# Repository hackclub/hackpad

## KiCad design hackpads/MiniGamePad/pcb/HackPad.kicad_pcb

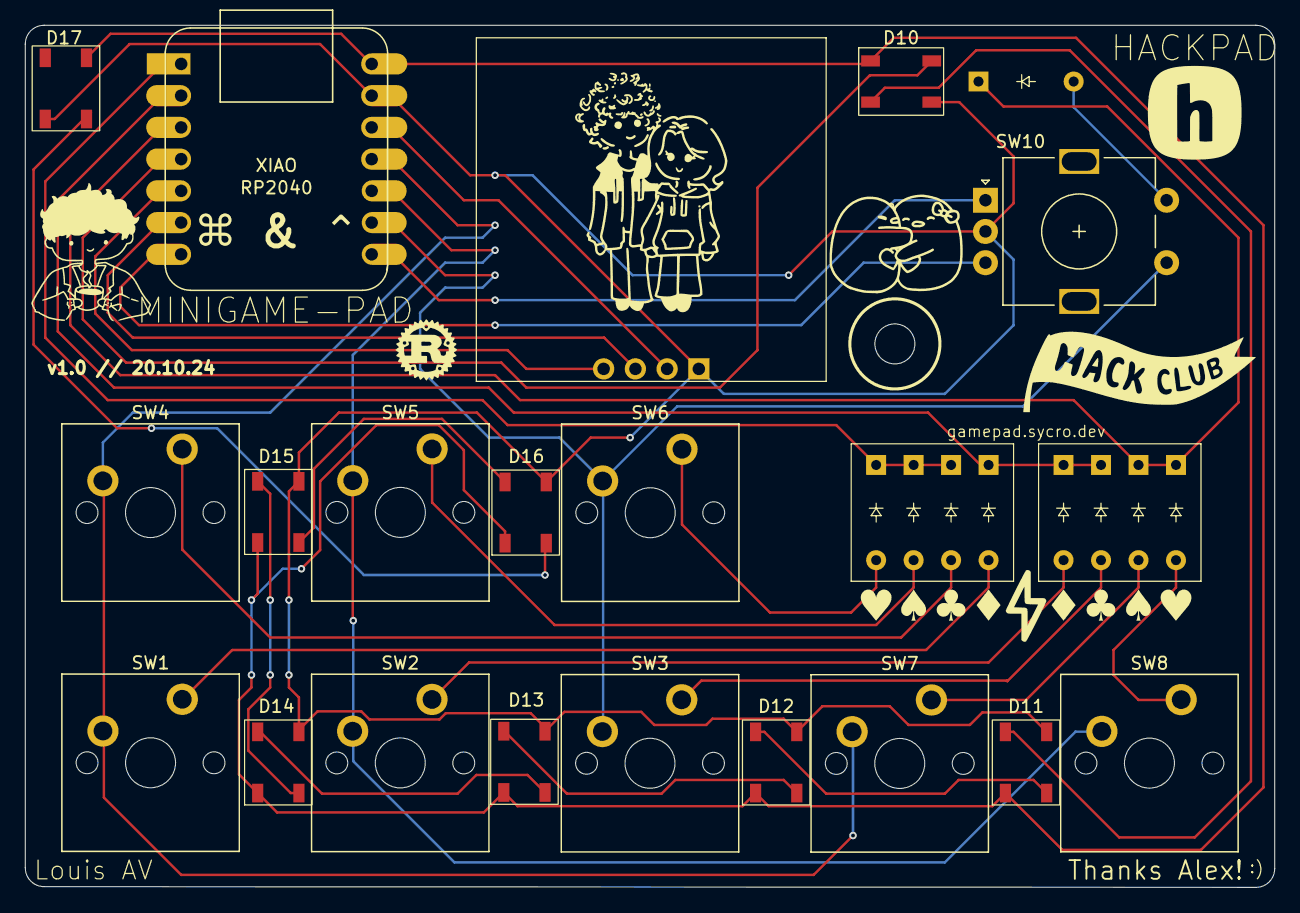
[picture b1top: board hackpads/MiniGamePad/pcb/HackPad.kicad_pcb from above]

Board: 2 copper layers, 100.0 x 69.0 mm, 28 parts (0 on the bottom side), 30 nets.

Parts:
D1, D2, D3, D4, D5, D6, D7, D8, D9: D; Diode_DO-35
D10, D11, D12, D13, D14, D15, D16, D17: WS2812B; LED_WS2812B
J1: OLED_128x64
SW1, SW2, SW3, SW4, SW5, SW6, SW7, SW8: SW_Push_45deg; MX_PCB_1.00u
SW10: RotaryEncoder_Switch; RotaryEncoder_Alps_EC11E-Switch_Vertical_H20mm
U1: MOUDLE-SEEEDUINO-XIAO; XIAO-Generic-Hybrid-14P-2.54-21X17.8MM

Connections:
+3.3V: J1.2 (VCC), U1.12 (3V3)
+5V: D10.1 (VDD), D11.1 (VDD), D12.1 (VDD), D13.1 (VDD), D14.1 (VDD), D15.1 (VDD), D16.1 (VDD), D17.1 (VDD), U1.14 (5V)
Column 1: SW1.1, SW4.1, SW7.1, U1.11 (PA6_A10_D10_MOSI)
Column 2: SW2.1, SW5.1, SW8.1, U1.10 (PA5_A9_D9_MISO)
Column 3: SW3.1, SW6.1, SW10.S1, U1.9 (PA7_A8_D8_SCK)
EC11A: SW10.A, U1.8 (PB09_A7_D7_RX)
EC11B: SW10.B, U1.7 (PB08_A6_D6_TX)
EC11SWB: D9.2 (A), SW10.S2
GND: D10.3 (VSS), D11.3 (VSS), D12.3 (VSS), D13.3 (VSS), D14.3 (VSS), D15.3 (VSS), D16.3 (VSS), D17.3 (VSS), J1.1 (GND), SW10.C, U1.13 (GND)
unnamed: D1.2 (A), SW1.2
unnamed: D2.2 (A), SW2.2
unnamed: D3.2 (A), SW3.2
unnamed: D4.2 (A), SW4.2
unnamed: D5.2 (A), SW5.2
unnamed: D6.2 (A), SW6.2
unnamed: D7.2 (A), SW7.2
unnamed: D8.2 (A), SW8.2
unnamed: D10.2 (DOUT), D11.4 (DIN)
unnamed: D11.2 (DOUT), D12.4 (DIN)
unnamed: D12.2 (DOUT), D13.4 (DIN)
unnamed: D13.2 (DOUT), D14.4 (DIN)
unnamed: D14.2 (DOUT), D15.4 (DIN)
unnamed: D15.2 (DOUT), D16.4 (DIN)
unnamed: D16.2 (DOUT), D17.4 (DIN)
RGB: D10.4 (DIN), U1.4 (PA11_A3_D3)
Row 1: D1.1 (K), D2.1 (K), D3.1 (K), U1.2 (PA4_A1_D1)
Row 2: D4.1 (K), D5.1 (K), D6.1 (K), U1.1 (PA02_A0_D0)
Row 3: D7.1 (K), D8.1 (K), D9.1 (K), U1.3 (PA10_A2_D2)
SCL: J1.3 (SCL), U1.6 (PA9_A5_D5_SCL)
SDA: J1.4 (SDA), U1.5 (PA8_A4_D4_SDA)

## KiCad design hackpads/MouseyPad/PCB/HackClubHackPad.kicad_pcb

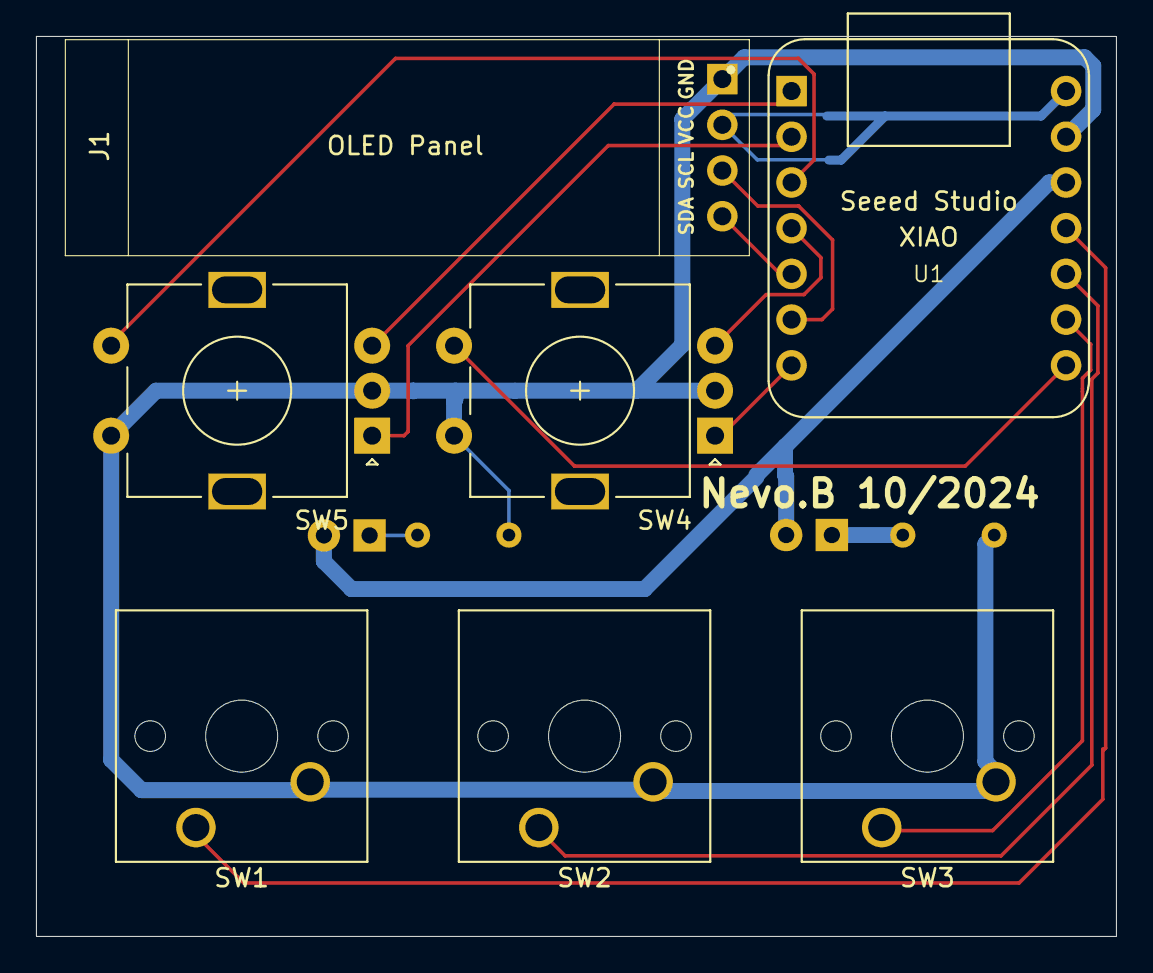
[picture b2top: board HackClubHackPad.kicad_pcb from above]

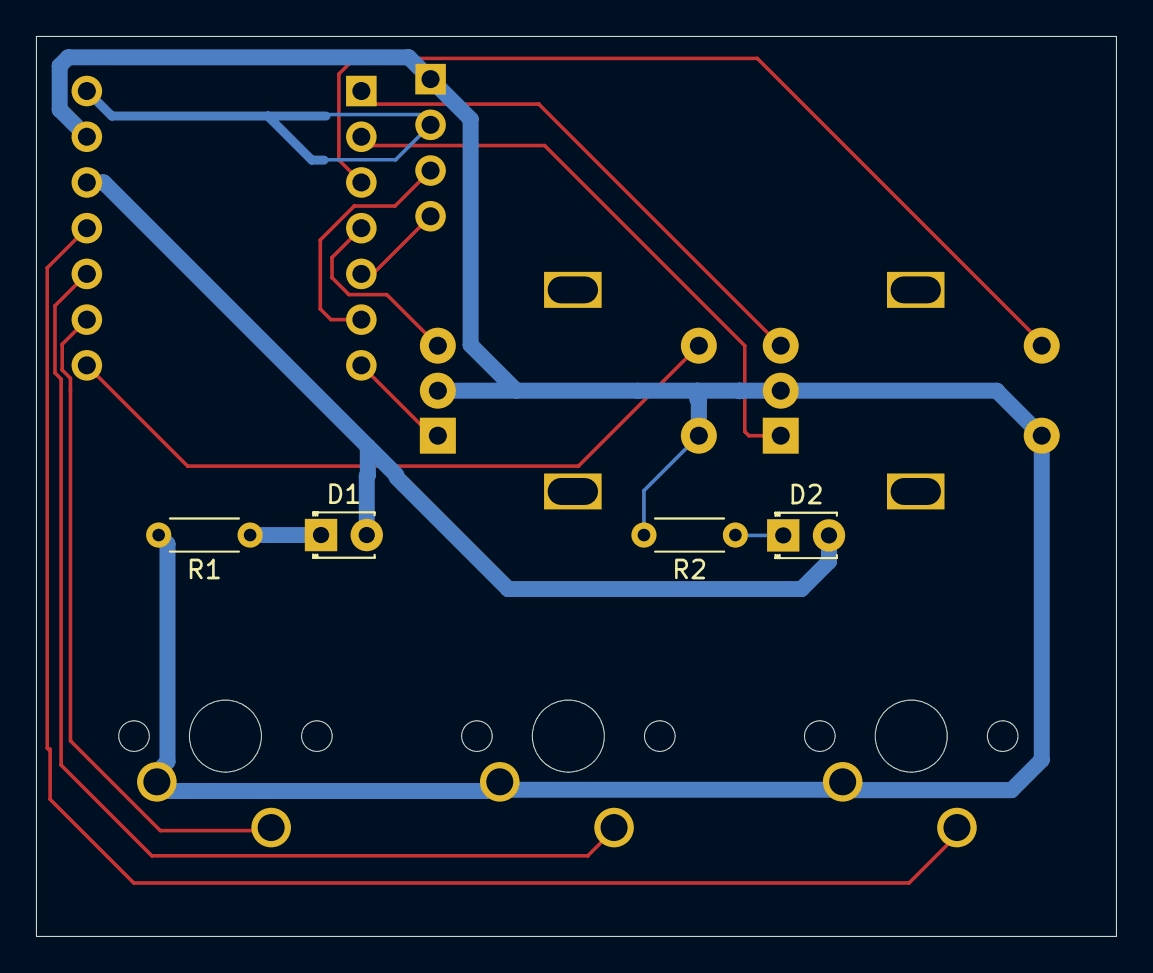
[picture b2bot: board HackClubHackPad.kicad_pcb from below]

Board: 2 copper layers, 60.0 x 50.0 mm, 11 parts (4 on the bottom side), 16 nets.

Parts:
D1, D2: LED; LED_D1.8mm_W3.3mm_H2.4mm
J1: Conn_01x04; SSD1306-0.91-OLED-4pin-128x32
R1, R2: 36; R_Axial_DIN0204_L3.6mm_D1.6mm_P5.08mm_Horizontal
SW1, SW2, SW3: SW_Push; SW_Cherry_MX_1.00u_PCB
SW4, SW5: RotaryEncoder_Switch; RotaryEncoder_Alps_EC11E-Switch_Vertical_H20mm
U1: Seeed Studio XIAO SAMD21; XIAO-Generic-Thruhole-14P-2.54-21X17.8MM

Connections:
+3.3V: D1.2 (A), D2.2 (A), U1.12 (3V3)
+5V: J1.2, U1.14 (5V)
EC11(2)A: SW4.A, U1.7 (PB08_A6_D6_TX)
EC11(2)B: SW4.B, U1.4 (PA11_A3_D3)
EC11(2)SW: SW4.S1, U1.8 (PB09_A7_D7_RX)
EC11A: SW5.A, U1.2 (PA4_A1_D1)
EC11B: SW5.B, U1.1 (PA02_A0_D0)
EC11SW: SW5.S1, U1.3 (PA10_A2_D2)
GND: J1.1, R1.2, R2.2, SW1.2, SW2.2, SW3.2, SW4.C, SW4.S2, SW5.C, SW5.S2, U1.13 (GND)
unnamed: D1.1 (K), R1.1
unnamed: D2.1 (K), R2.1
SCL: J1.3, U1.6 (PA9_A5_D5_SCL)
SDA: J1.4, U1.5 (PA8_A4_D4_SDA)
SW1: SW1.1, U1.11 (PA6_A10_D10_MOSI)
SW2: SW2.1, U1.10 (PA5_A9_D9_MISO)
SW3: SW3.1, U1.9 (PA7_A8_D8_SCK)

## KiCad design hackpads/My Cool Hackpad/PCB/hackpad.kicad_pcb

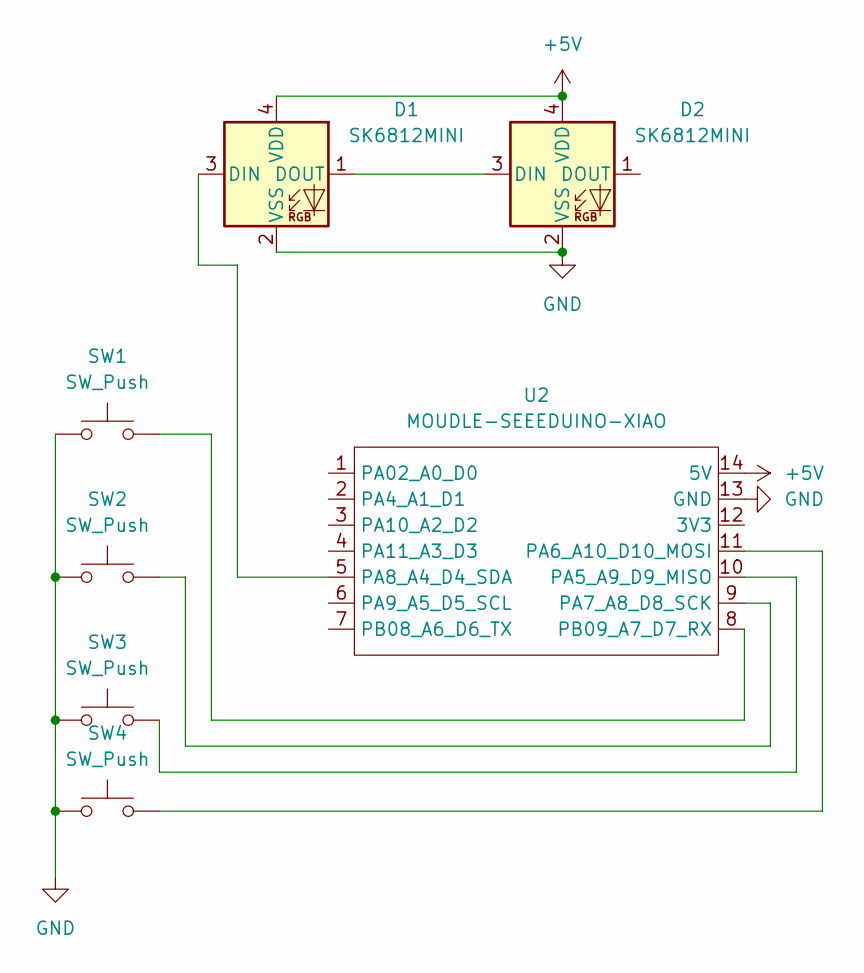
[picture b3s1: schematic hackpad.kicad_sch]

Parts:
D1, D2: SK6812MINI; LED_SK6812MINI_PLCC4_3.5x3.5mm_P1.75mm
SW1, SW2, SW3, SW4: SW_Push; SW_Cherry_MX_PCB_1.00u
U2: MOUDLE-SEEEDUINO-XIAO; MOUDLE14P-2.54-21X17.8MM

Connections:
+5V: D1.4 (VDD), D2.4 (VDD), U2.14 (5V)
GND: D1.2 (VSS), D2.2 (VSS), SW1.1, SW2.1, SW3.1, SW4.1, U2.13 (GND)
unnamed: D1.3 (DIN), U2.5 (PA8_A4_D4_SDA)
unnamed: D1.1 (DOUT), D2.3 (DIN)
unnamed: SW3.2, U2.10 (PA5_A9_D9_MISO)
unnamed: SW4.2, U2.11 (PA6_A10_D10_MOSI)
unnamed: SW2.2, U2.9 (PA7_A8_D8_SCK)
unnamed: SW1.2, U2.8 (PB09_A7_D7_RX)

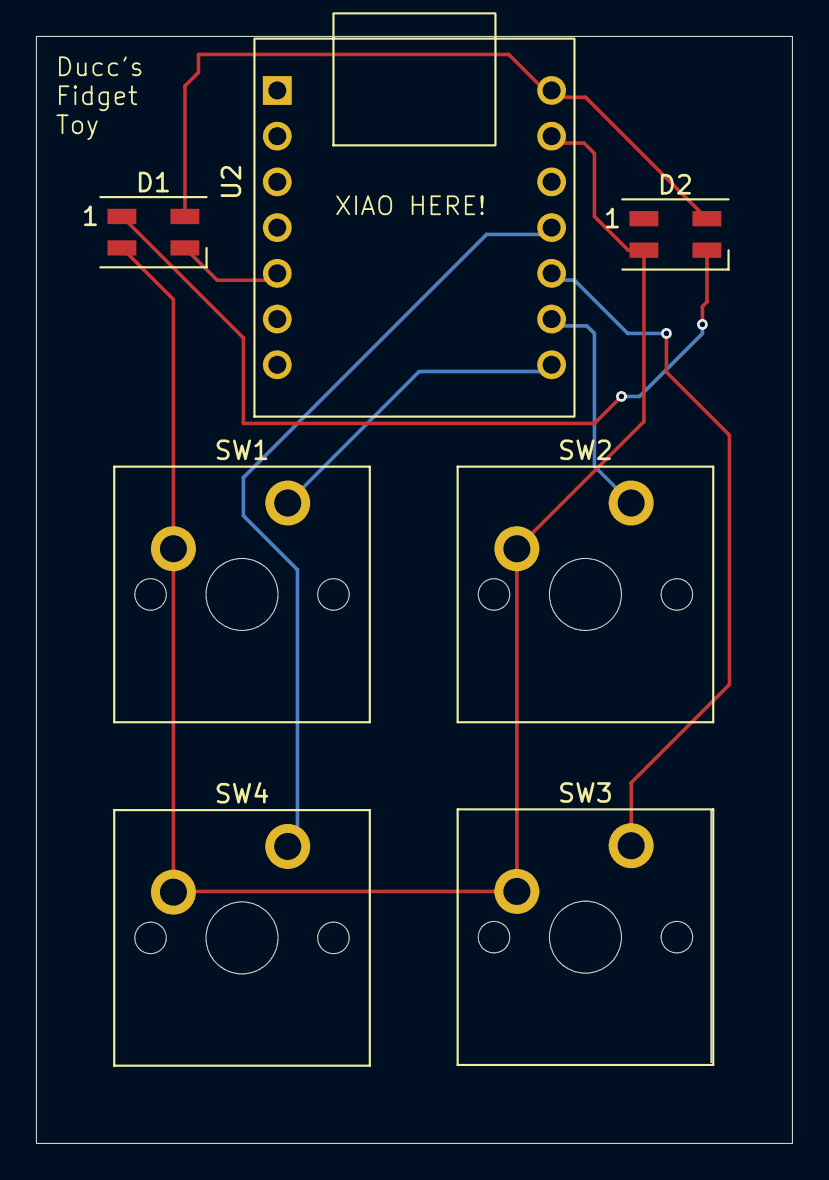
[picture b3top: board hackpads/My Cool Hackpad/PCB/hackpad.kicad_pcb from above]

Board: 2 copper layers, 42.0 x 61.5 mm, 7 parts (0 on the bottom side), 8 nets.

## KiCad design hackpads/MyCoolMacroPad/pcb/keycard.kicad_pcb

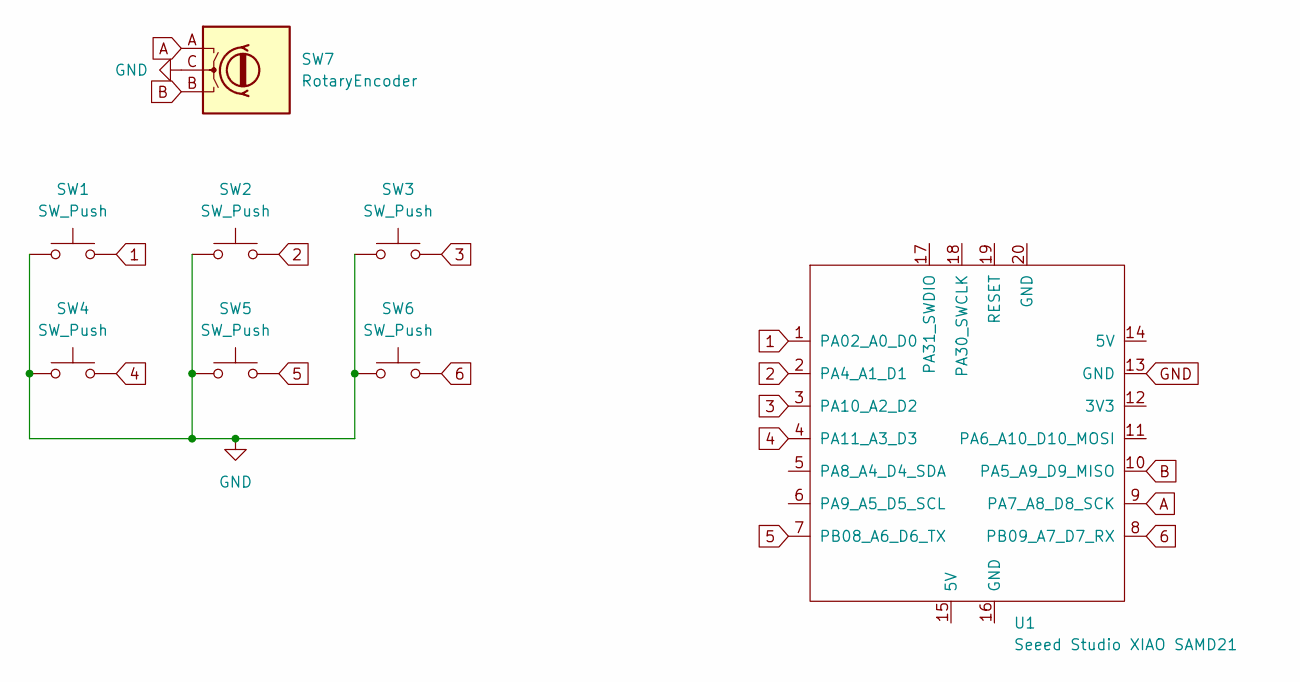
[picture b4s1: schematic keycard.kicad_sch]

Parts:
SW1, SW2, SW3, SW4, SW5, SW6: SW_Push; SW_Cherry_MX_1.00u_PCB
SW7: RotaryEncoder; RotaryEncoder_Alps_EC11E-Switch_Vertical_H20mm
U1: Seeed Studio XIAO SAMD21; XIAO-Generic-Thruhole-14P-2.54-21X17.8MM

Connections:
1: SW1.2, U1.1 (PA02_A0_D0)
2: SW2.2, U1.2 (PA4_A1_D1)
3: SW3.2, U1.3 (PA10_A2_D2)
4: SW4.2, U1.4 (PA11_A3_D3)
5: SW5.2, U1.7 (PB08_A6_D6_TX)
6: SW6.2, U1.8 (PB09_A7_D7_RX)
A: SW7.A, U1.9 (PA7_A8_D8_SCK)
B: SW7.B, U1.10 (PA5_A9_D9_MISO)
GND: SW1.1, SW2.1, SW3.1, SW4.1, SW5.1, SW6.1, SW7.C, U1.13 (GND)

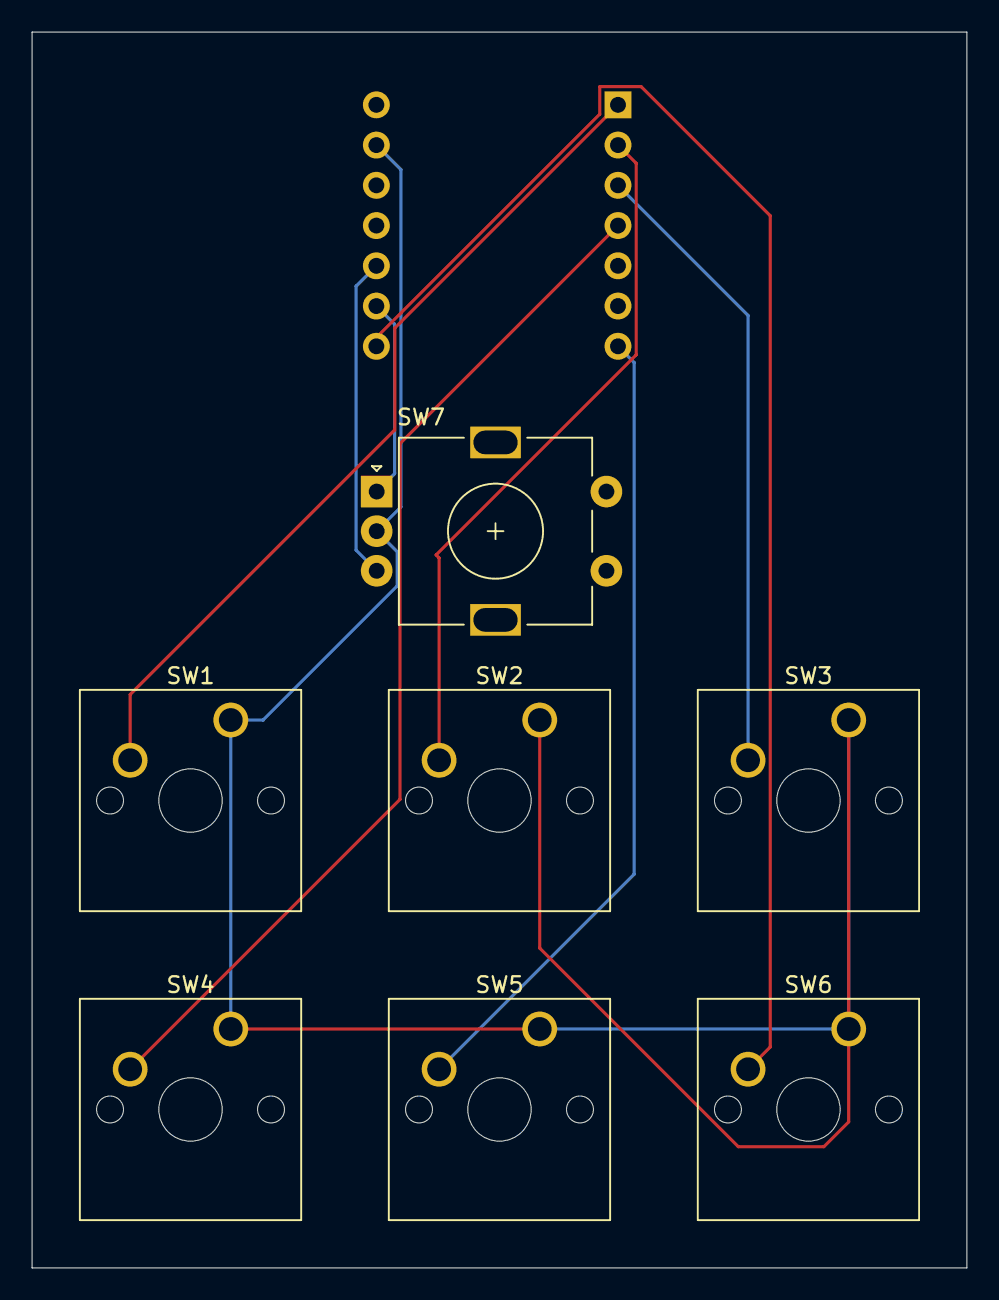
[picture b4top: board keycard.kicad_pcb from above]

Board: 2 copper layers, 59.0 x 78.0 mm, 8 parts (1 on the bottom side), 9 nets.

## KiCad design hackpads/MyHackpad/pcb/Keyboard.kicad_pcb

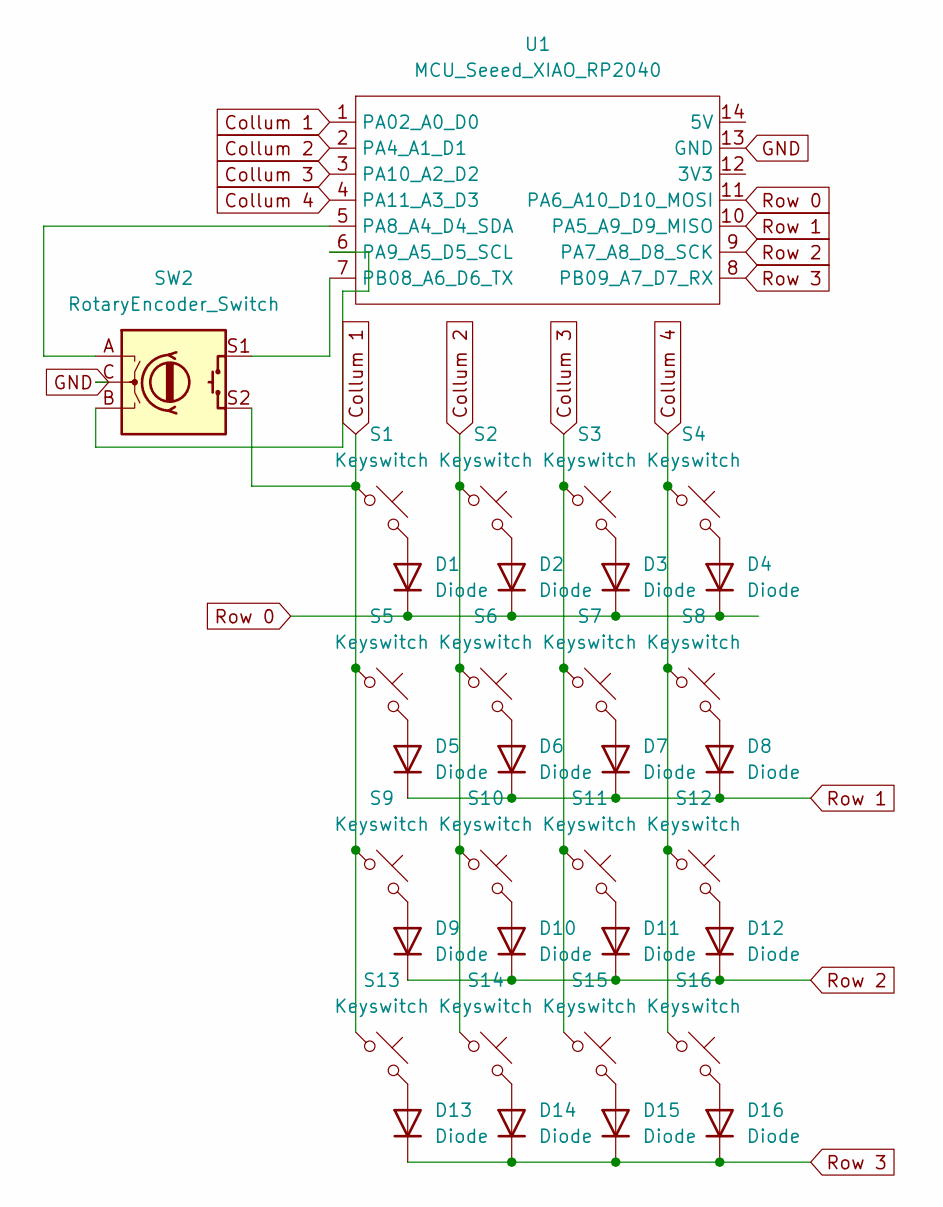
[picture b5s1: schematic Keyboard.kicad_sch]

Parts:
D1, D2, D3, D4, D5, D6, D7, D8, D9, D10, D11, D12, D13, D14, D15, D16: Diode; Diode_DO-35
S1, S2, S3, S4, S5, S6, S7, S8, S9, S10, S11, S12, S13, S14, S15, S16: Keyswitch; MX_PCB_1.00u
SW2: RotaryEncoder_Switch; Encoder_EC11_MX
U1: MCU_Seeed_XIAO_RP2040; Seeed_XIAO_RP2040

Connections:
Collum 1: S1.1, S5.1, S9.1, S13.1, SW2.S2, U1.1 (PA02_A0_D0)
Collum 2: S2.1, S6.1, S10.1, S14.1, U1.2 (PA4_A1_D1)
Collum 3: S3.1, S7.1, S11.1, S15.1, U1.3 (PA10_A2_D2)
Collum 4: S4.1, S8.1, S12.1, S16.1, U1.4 (PA11_A3_D3)
GND: SW2.C, U1.13 (GND)
unnamed: D1.2 (A), S1.2
unnamed: D2.2 (A), S2.2
unnamed: D3.2 (A), S3.2
unnamed: D4.2 (A), S4.2
unnamed: D5.2 (A), S5.2
unnamed: D6.2 (A), S6.2
unnamed: D7.2 (A), S7.2
unnamed: D8.2 (A), S8.2
unnamed: D9.2 (A), S9.2
unnamed: D10.2 (A), S10.2
unnamed: D11.2 (A), S11.2
unnamed: D12.2 (A), S12.2
unnamed: D13.2 (A), S13.2
unnamed: D14.2 (A), S14.2
unnamed: D15.2 (A), S15.2
unnamed: D16.2 (A), S16.2
unnamed: SW2.A, U1.5 (PA8_A4_D4_SDA)
unnamed: SW2.B, U1.6 (PA9_A5_D5_SCL)
unnamed: SW2.S1, U1.7 (PB08_A6_D6_TX)
Row 0: D1.1 (K), D2.1 (K), D3.1 (K), D4.1 (K), U1.11 (PA6_A10_D10_MOSI)
Row 1: D5.1 (K), D6.1 (K), D7.1 (K), D8.1 (K), U1.10 (PA5_A9_D9_MISO)
Row 2: D9.1 (K), D10.1 (K), D11.1 (K), D12.1 (K), U1.9 (PA7_A8_D8_SCK)
Row 3: D13.1 (K), D14.1 (K), D15.1 (K), D16.1 (K), U1.8 (PB09_A7_D7_RX)

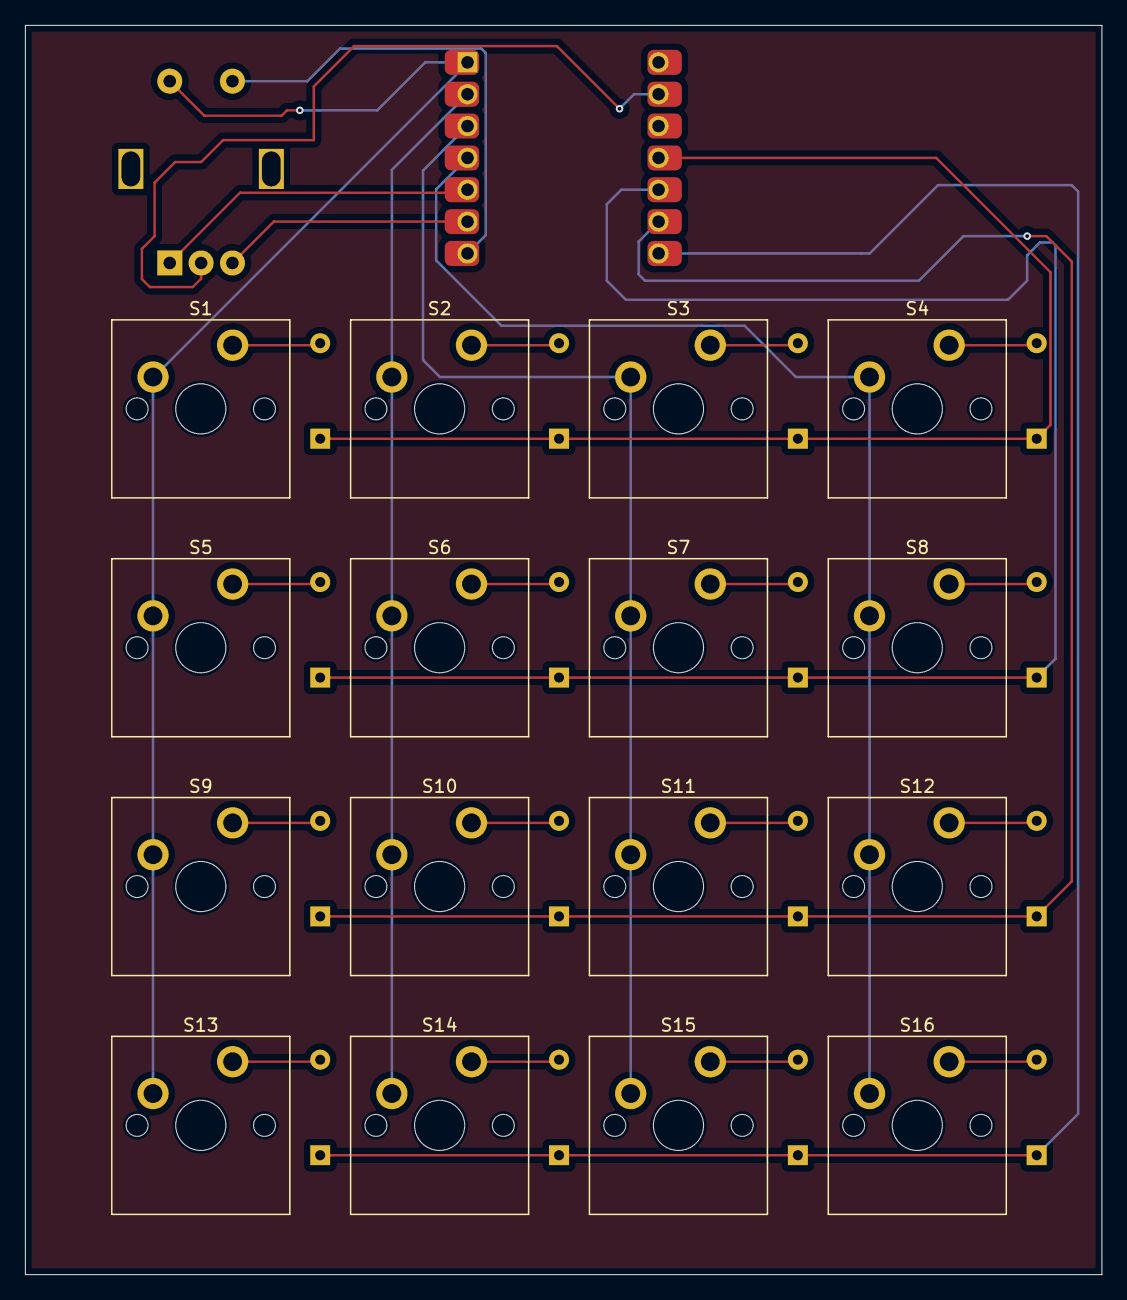
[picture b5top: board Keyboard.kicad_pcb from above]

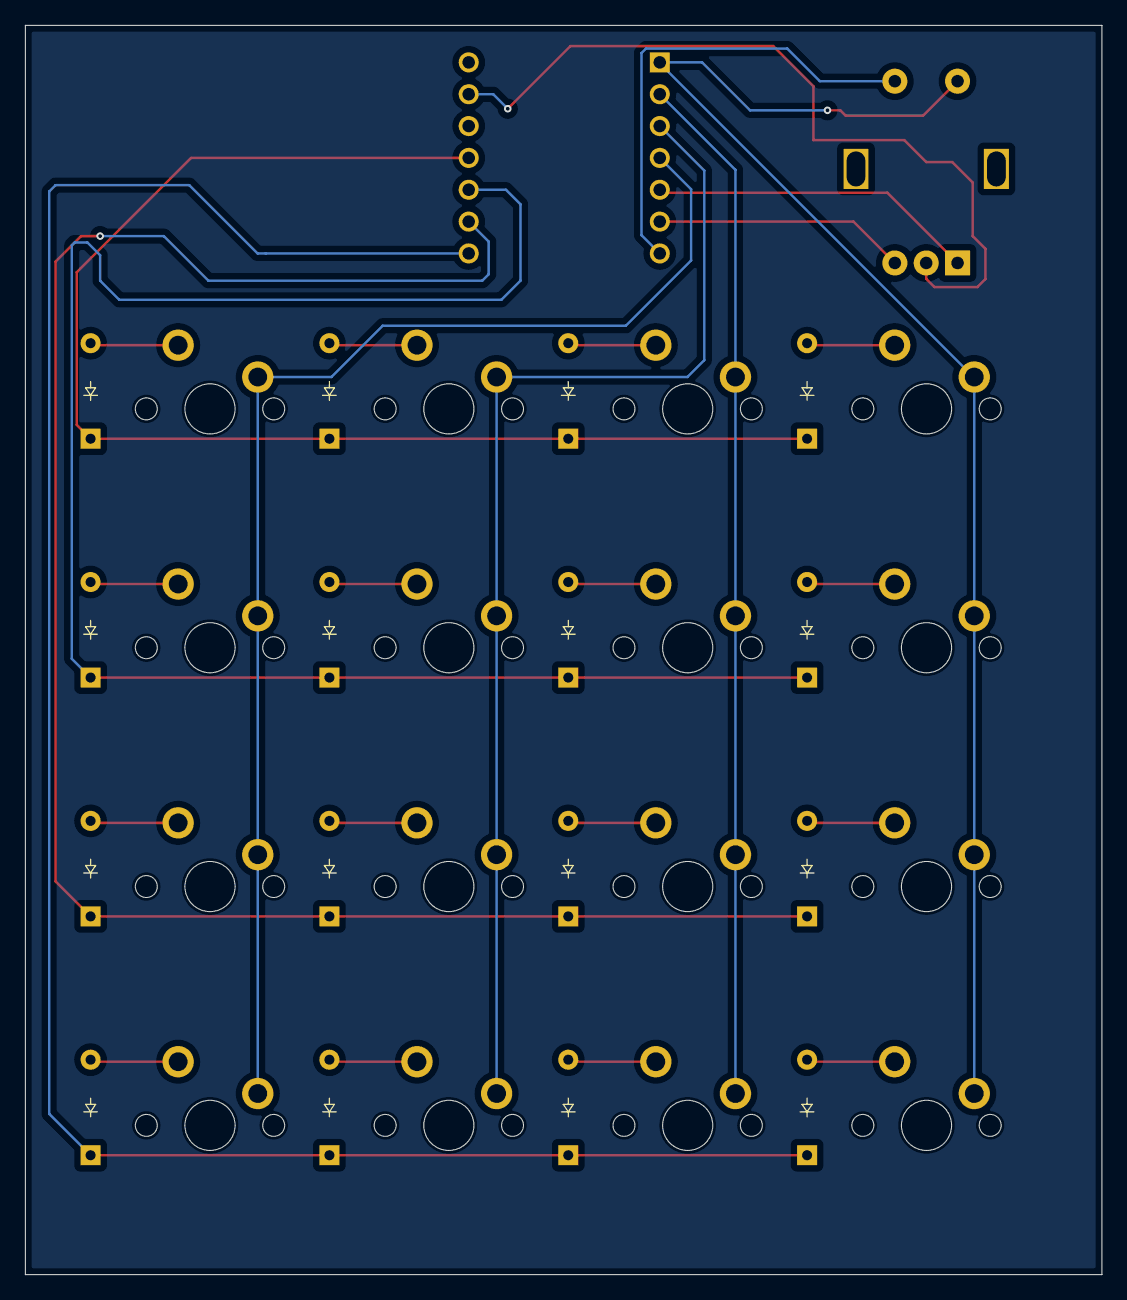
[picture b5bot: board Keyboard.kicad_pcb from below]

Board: 2 copper layers, 85.9 x 99.6 mm, 34 parts (16 on the bottom side), 28 nets.

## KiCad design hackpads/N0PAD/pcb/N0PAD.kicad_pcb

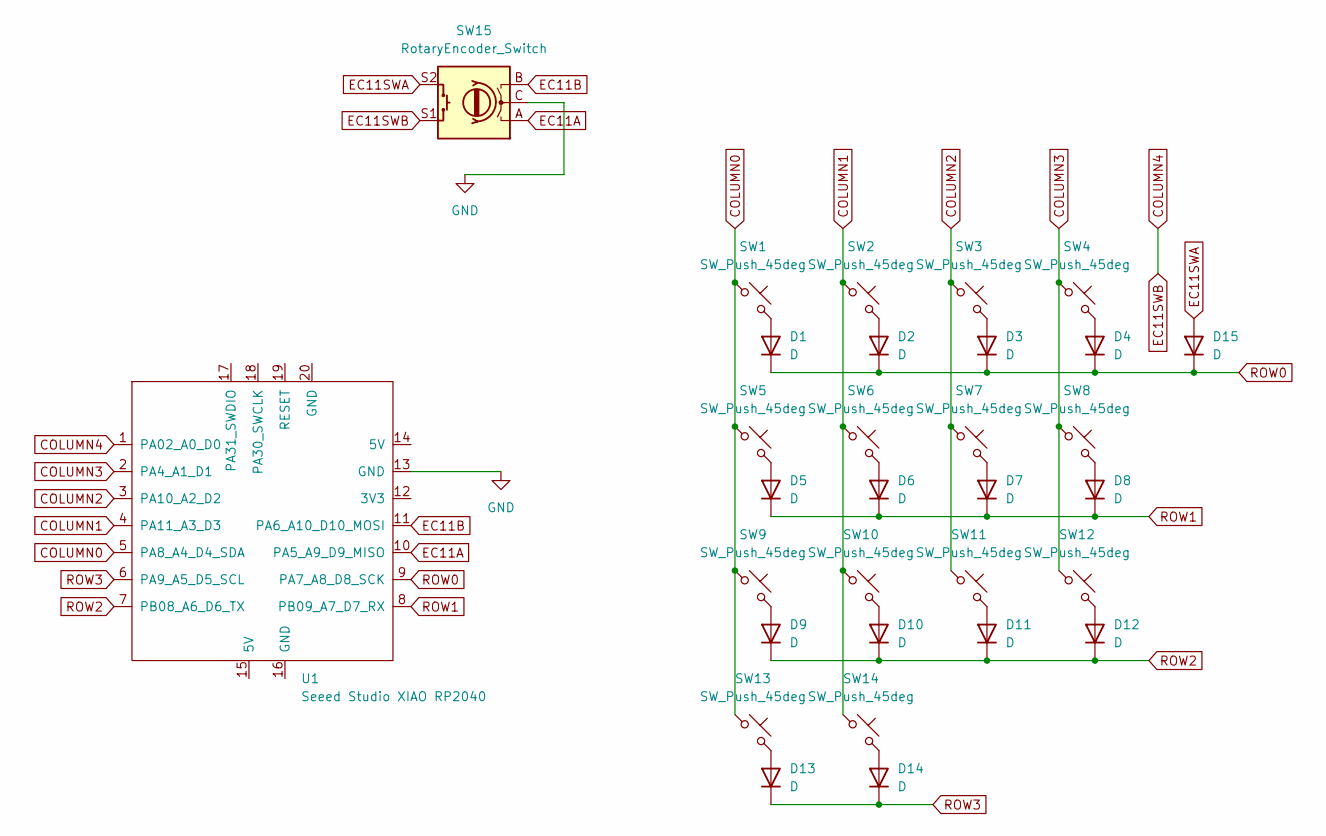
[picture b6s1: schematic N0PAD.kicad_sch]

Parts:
D1, D2, D3, D4, D5, D6, D7, D8, D9, D10, D11, D12, D13, D14, D15: D; D_DO-35_SOD27_P7.62mm_Horizontal
SW1, SW2, SW3, SW4, SW5, SW6, SW7, SW8, SW9, SW10, SW11, SW12, SW13, SW14: SW_Push_45deg; SW_Cherry_MX_1.00u_PCB
SW15: RotaryEncoder_Switch; RotaryEncoder_Alps_EC11E-Switch_Vertical_H20mm
U1: Seeed Studio XIAO RP2040; XIAO-Generic-Thruhole-14P-2.54-21X17.8MM

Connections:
COLUMN0: SW1.1, SW5.1, SW9.1, SW13.1, U1.5 (PA8_A4_D4_SDA)
COLUMN1: SW2.1, SW6.1, SW10.1, SW14.1, U1.4 (PA11_A3_D3)
COLUMN2: SW3.1, SW7.1, SW11.1, U1.3 (PA10_A2_D2)
COLUMN3: SW4.1, SW8.1, SW12.1, U1.2 (PA4_A1_D1)
COLUMN4: SW15.S1, U1.1 (PA02_A0_D0)
EC11A: SW15.A, U1.10 (PA5_A9_D9_MISO)
EC11B: SW15.B, U1.11 (PA6_A10_D10_MOSI)
EC11SWA: D15.2 (A), SW15.S2
GND: SW15.C, U1.13 (GND)
unnamed: D1.2 (A), SW1.2
unnamed: D2.2 (A), SW2.2
unnamed: D3.2 (A), SW3.2
unnamed: D4.2 (A), SW4.2
unnamed: D5.2 (A), SW5.2
unnamed: D6.2 (A), SW6.2
unnamed: D7.2 (A), SW7.2
unnamed: D8.2 (A), SW8.2
unnamed: D9.2 (A), SW9.2
unnamed: D10.2 (A), SW10.2
unnamed: D11.2 (A), SW11.2
unnamed: D12.2 (A), SW12.2
unnamed: D13.2 (A), SW13.2
unnamed: D14.2 (A), SW14.2
ROW0: D1.1 (K), D2.1 (K), D3.1 (K), D4.1 (K), D15.1 (K), U1.9 (PA7_A8_D8_SCK)
ROW1: D5.1 (K), D6.1 (K), D7.1 (K), D8.1 (K), U1.8 (PB09_A7_D7_RX)
ROW2: D9.1 (K), D10.1 (K), D11.1 (K), D12.1 (K), U1.7 (PB08_A6_D6_TX)
ROW3: D13.1 (K), D14.1 (K), U1.6 (PA9_A5_D5_SCL)

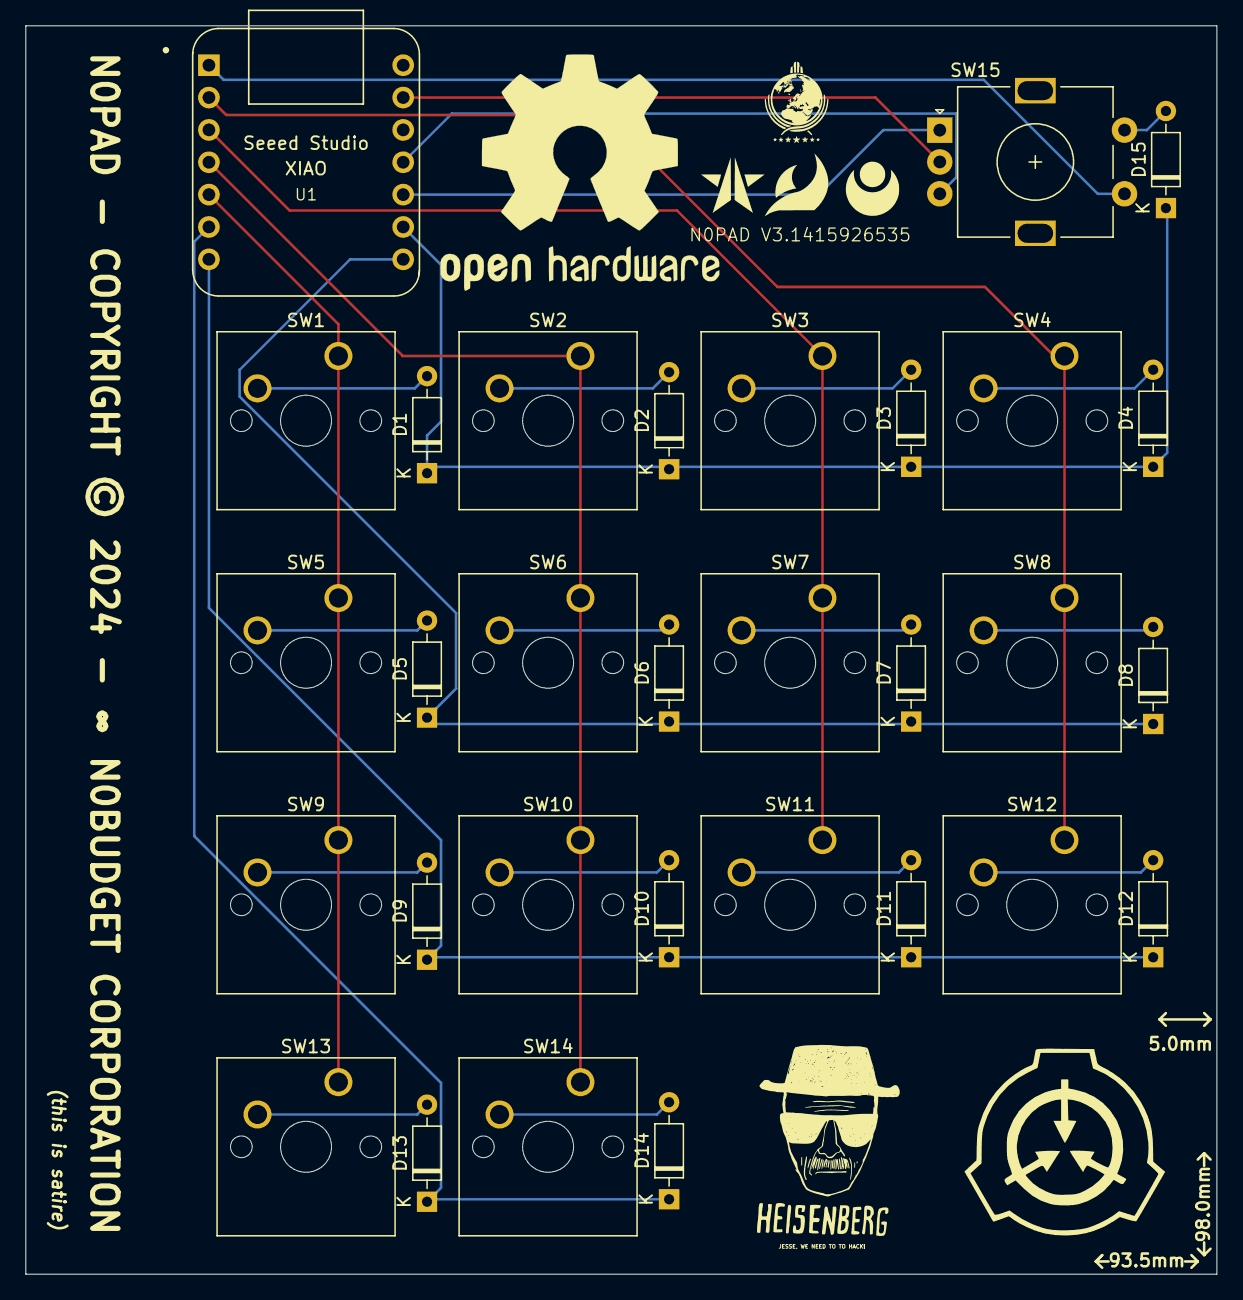
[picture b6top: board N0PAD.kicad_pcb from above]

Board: 2 copper layers, 93.5 x 98.0 mm, 31 parts (0 on the bottom side), 27 nets.

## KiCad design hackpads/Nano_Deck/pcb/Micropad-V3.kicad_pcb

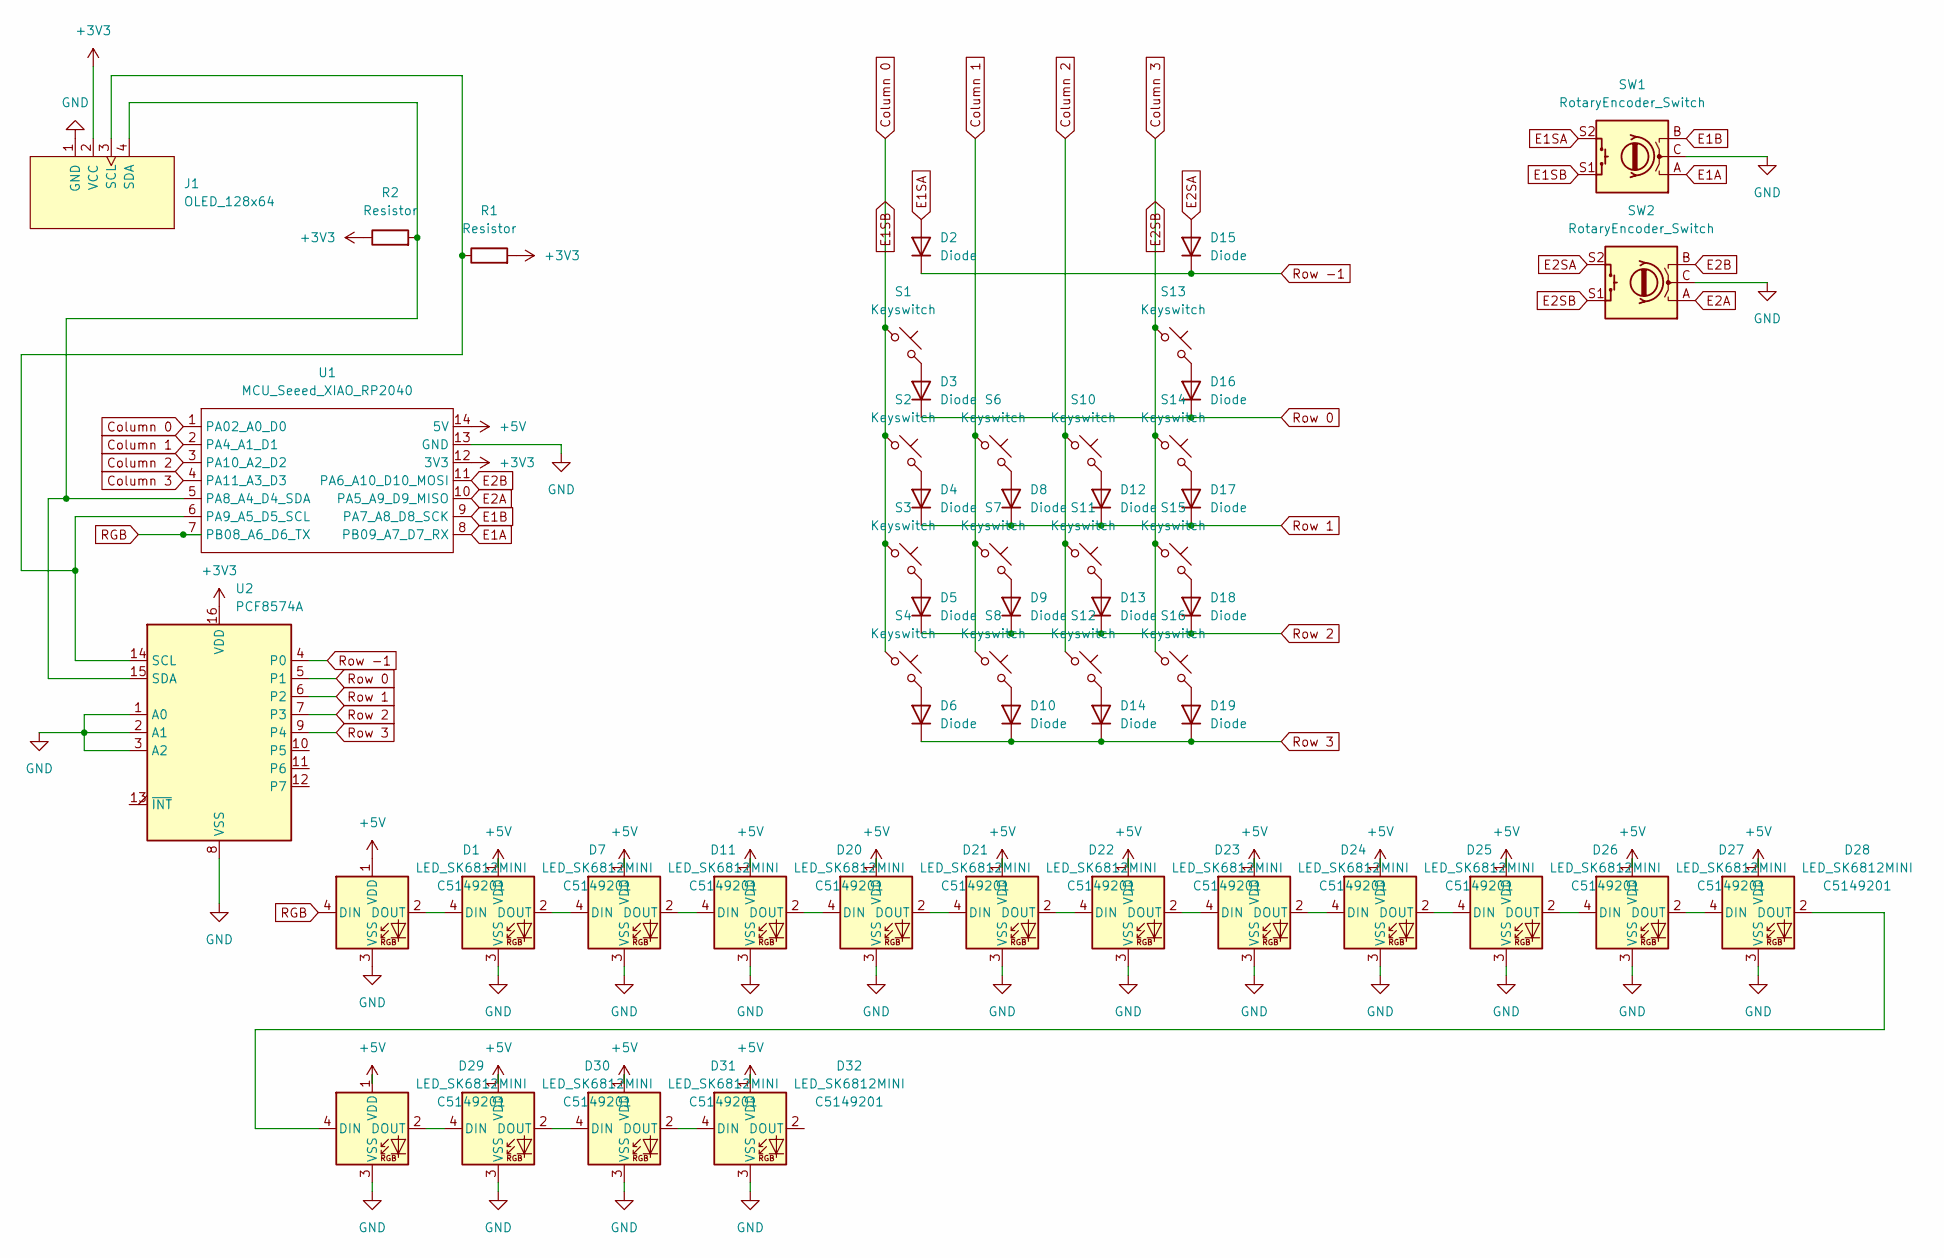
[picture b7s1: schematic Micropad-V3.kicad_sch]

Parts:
D1, D7, D11, D20, D21, D22, D23, D24, D25, D26, D27, D28, D29, D30, D31, D32: LED_SK6812MINI; LCSC C5149201
D2, D3, D4, D5, D6, D8, D9, D10, D12, D13, D14, D15, D16, D17, D18, D19: Diode; Diode_DO-35
J1: OLED_128x64
R1, R2: Resistor; R_Axial_DIN0204_L3.6mm_D1.6mm_P5.08mm_Horizontal
S1, S2, S3, S4, S6, S7, S8, S10, S11, S12, S13, S14, S15, S16: Keyswitch; MX_PCB_1.00u
SW1, SW2: RotaryEncoder_Switch; RotaryEncoder_Alps_EC11E-Switch_Vertical_H20mm
U1: MCU_Seeed_XIAO_RP2040; Seeed_XIAO_RP2040
U2: PCF8574A; N16

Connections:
+3V3: J1.2 (VCC), R1.2, R2.1, U1.12 (3V3), U2.16 (VDD)
+5V: D1.1 (VDD), D7.1 (VDD), D11.1 (VDD), D20.1 (VDD), D21.1 (VDD), D22.1 (VDD), D23.1 (VDD), D24.1 (VDD), D25.1 (VDD), D26.1 (VDD), D27.1 (VDD), D28.1 (VDD), D29.1 (VDD), D30.1 (VDD), D31.1 (VDD), D32.1 (VDD), U1.14 (5V)
Column 0: S1.1, S2.1, S3.1, S4.1, SW1.S1, U1.1 (PA02_A0_D0)
Column 1: S6.1, S7.1, S8.1, U1.2 (PA4_A1_D1)
Column 2: S10.1, S11.1, S12.1, U1.3 (PA10_A2_D2)
Column 3: S13.1, S14.1, S15.1, S16.1, SW2.S1, U1.4 (PA11_A3_D3)
E1A: SW1.A, U1.8 (PB09_A7_D7_RX)
E1B: SW1.B, U1.9 (PA7_A8_D8_SCK)
E1SA: D2.2 (A), SW1.S2
E2A: SW2.A, U1.10 (PA5_A9_D9_MISO)
E2B: SW2.B, U1.11 (PA6_A10_D10_MOSI)
E2SA: D15.2 (A), SW2.S2
GND: D1.3 (VSS), D7.3 (VSS), D11.3 (VSS), D20.3 (VSS), D21.3 (VSS), D22.3 (VSS), D23.3 (VSS), D24.3 (VSS), D25.3 (VSS), D26.3 (VSS), D27.3 (VSS), D28.3 (VSS), D29.3 (VSS), D30.3 (VSS), D31.3 (VSS), D32.3 (VSS), J1.1 (GND), SW1.C, SW2.C, U1.13 (GND), U2.1 (A0), U2.2 (A1), U2.3 (A2), U2.8 (VSS)
unnamed: D1.2 (DOUT), D7.4 (DIN)
unnamed: D3.2 (A), S1.2
unnamed: D4.2 (A), S2.2
unnamed: D5.2 (A), S3.2
unnamed: D6.2 (A), S4.2
unnamed: D8.2 (A), S6.2
unnamed: D9.2 (A), S7.2
unnamed: D10.2 (A), S8.2
unnamed: D7.2 (DOUT), D11.4 (DIN)
unnamed: D11.2 (DOUT), D20.4 (DIN)
unnamed: D12.2 (A), S10.2
unnamed: D13.2 (A), S11.2
unnamed: D14.2 (A), S12.2
unnamed: D16.2 (A), S13.2
unnamed: D17.2 (A), S14.2
unnamed: D18.2 (A), S15.2
unnamed: D19.2 (A), S16.2
unnamed: D20.2 (DOUT), D21.4 (DIN)
unnamed: D21.2 (DOUT), D22.4 (DIN)
unnamed: D22.2 (DOUT), D23.4 (DIN)
unnamed: D23.2 (DOUT), D24.4 (DIN)
unnamed: D24.2 (DOUT), D25.4 (DIN)
unnamed: D25.2 (DOUT), D26.4 (DIN)
unnamed: D26.2 (DOUT), D27.4 (DIN)
unnamed: D27.2 (DOUT), D28.4 (DIN)
unnamed: D28.2 (DOUT), D29.4 (DIN)
unnamed: D29.2 (DOUT), D30.4 (DIN)
unnamed: D30.2 (DOUT), D31.4 (DIN)
unnamed: D31.2 (DOUT), D32.4 (DIN)
unnamed: J1.3 (SCL), R1.1, U1.6 (PA9_A5_D5_SCL), U2.14 (SCL)
unnamed: J1.4 (SDA), R2.2, U1.5 (PA8_A4_D4_SDA), U2.15 (SDA)
RGB: D1.4 (DIN), U1.7 (PB08_A6_D6_TX)
Row 0: D3.1 (K), D16.1 (K), U2.5 (P1)
Row 1: D4.1 (K), D8.1 (K), D12.1 (K), D17.1 (K), U2.6 (P2)
Row 2: D5.1 (K), D9.1 (K), D13.1 (K), D18.1 (K), U2.7 (P3)
Row 3: D6.1 (K), D10.1 (K), D14.1 (K), D19.1 (K), U2.9 (P4)
Row -1: D2.1 (K), D15.1 (K), U2.4 (P0)

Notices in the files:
hackpads/N0PAD/pcb/N0PAD.kicad_pcb:
N0PAD - COPYRIGHT © 2024 - ∞ N0BUDGET CORPORATION
